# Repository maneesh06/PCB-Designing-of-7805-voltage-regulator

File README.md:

# PCB-Designing-of-7805-voltage-regulator
In this project I make a PCB design of 7805 voltage regulator in Kicad.

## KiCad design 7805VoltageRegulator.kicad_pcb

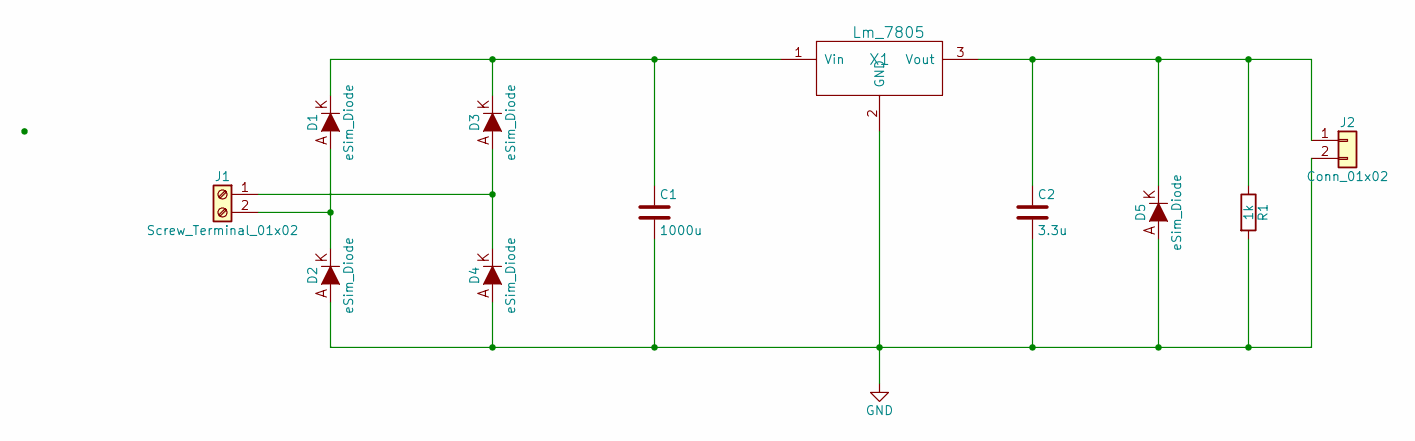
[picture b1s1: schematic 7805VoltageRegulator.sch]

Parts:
C1: 1000u; CP_Radial_D5.0mm_P2.50mm
C2: 3.3u; C_Disc_D3.0mm_W2.0mm_P2.50mm
D1, D2, D3, D4, D5: eSim_Diode; D_T-1_P5.08mm_Horizontal
J1: Screw_Terminal_01x02; TerminalBlock_Altech_AK300-2_P5.00mm
J2: Conn_01x02; Pin_Header_Straight_1x02_Pitch2.54mm
R1: 1k; R_Axial_DIN0207_L6.3mm_D2.5mm_P10.16mm_Horizontal
X1: Lm_7805; TO-220-3_Vertical

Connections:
GND: C1.2, C2.2, D2.1 (A), D4.1 (A), D5.1 (A), J2.2, R1.2, X1.2 (GND)
unnamed: C1.1, D1.2 (K), D3.2 (K), X1.1 (Vin)
unnamed: C2.1, D5.2 (K), J2.1, R1.1, X1.3 (Vout)
unnamed: D1.1 (A), D2.2 (K), J1.2
unnamed: D3.1 (A), D4.2 (K), J1.1

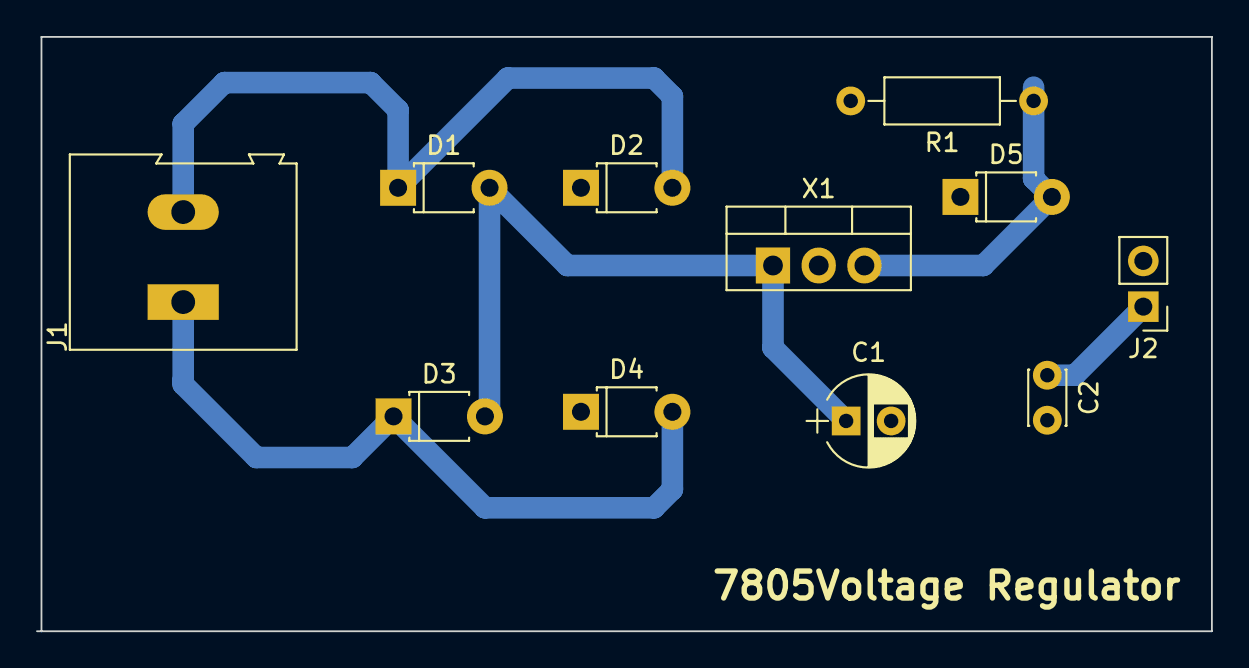
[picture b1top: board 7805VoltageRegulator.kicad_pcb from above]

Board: 2 copper layers, 65.3 x 33.0 mm, 11 parts (0 on the bottom side), 5 nets.
